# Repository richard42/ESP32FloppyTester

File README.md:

# ESP32_FloppyTester README

## What it is

The ESP32_FloppyTester is an open-source hardware/software project which aims to create a software-based floppy drive controller and tester with very low-cost hardware.  The materials cost for the interface board is under 10 dollars, and aside from a floppy drive cable the only other part necessary is an ESP32 development board, which can also be had for under 10 dollars.

The user communicates with the ESP32_FloppyTester via a serial monitor program on a PC or laptop, connected to the ESP32 development board by a USB cable.

The user gives commands to the ESP32_FloppyTester through the serial terminal, and as the desired operations are performed, statistics and results are sent back to the user.

The focus of this project is creating an easily-hackable tool which can be used in the diagnosis and repair of vintage 3.5" and 5.25" floppy drives.

## What it is NOT

The ESP32_FloppyTester is not designed to read or write disk image files for copying or preservation of digital media.  There are numerous projects already available which serve this function well.  Before creating the ESP32_FloppyTester, I purchased and used the KryoFlux, the FluxEngine, and the GreaseWeazle. These are all very capable products for recording and capturing data from floppy drives.

The focus of this project is to give the user very low-level control over the operation of a floppy drive so that if it is defective, the nature and root cause of the defect(s) may be determined and remedied.

## Contents

* [Hardware Warning](#hardware-warning)
* [Setup](#setup)
* [Basic Usage](#basic-usage)
* [Advanced Usage](#advanced-usage)
* [Caveats](caveats)

### Hardware Warning

There is one important flaw with the current interface board design, and users must be aware of this.

When the ESP32 microcontroller is being flashed by the ESP-IDF development system, all of its pins go into a high-impedance state with pull-up resistors.

As a result, all of the output lines will go active on any connected floppy drive. In particular, the SELECT, MOTOR ON, SIDE 1, and WRITE GATE lines will all be active during the ESP32 flashing process.

Because of this, if there is a disk inserted into the connected floppy drive, and it is not write protected, the track on side 1 which is under the drive head will be erased.

As a workaround, the user should always make sure that the drive has no disk in it when re-flashing the ESP32 software.

### Setup

To build the interface board, you may send the Gerber files in the "hardware" sub-directory to a printed-circuit board manufacturer such as PCBWay or JLCPCB. Order the remaining parts from digi-key and solder the board together once it all arrives. The "doc" sub-folder contains a Bill of Materials and pictures of the finished product.

The next step is to set up the [arduino IDE software](https://www.arduino.cc/en/software) and configure it for your ESP32 board. Then just load up the ESP32_FloppyTest.ino source code in your Arduino IDE and click the "Upload" button to compile the code and flash the ESP32 device. (But make sure there is no floppy disk in the drive, if you have one connected!)

Before connecting a drive the first time, it is good to check your soldering with the `TEST INPUT` and `TEST OUTPUT` commands.

When in the `TEST INPUT` mode, the software will poll for changes on any input pins and print the names and states of the pins when they change. You may use a jumper wire to bridge each input pin to a 5-volt supply, and observe the change via the serial monitor.

In the `TEST OUTPUT` mode, each output pin will oscillate with a binary pattern corresponding to the number of the pin. This pattern may be observed by connecting an oscilloscope to each output pin in turn. This test mode should never be used when a floppy drive is connected to the 34-pin connector, or **bad** things may happen.

Either test mode may be exited by sending a blank line or any characters to the ESP32.

### Basic Usage

Use the `HELP` command to view a list of all supported commands.

The floppy drive hardware interface, though common across many different drives and vintage computer systems, uses 5 different pins for selecting a particular drive and turning on its motor. The software currently defaults to a *shugart*-style interface with drive 0, such as would be configured for an internal drive on an Amiga computer. PC/Atari drives use different pins for drive selection, and so the user must use the `DETECT PINS` command to set the correct pins before anything else will work.

The `DETECT PINS` command activates each pin individually, and requests feedback from the user based upon how it affects the status of the floppy drive. At each step, the user must tell the ESP32_FloppyTester if the drive light has been illuminated, or if the motor has been activated. After answering all 5 prompts, the software will configure itself to properly address your floppy drive, and all of the other commands should then work.  If the detection fails and the drive light or motor never comes on, this indicates a failure in the drive's selection or motor control circuitry.

The next diagnostic step is to use the `DETECT RPM` command. A floppy disk must be inserted for this to work.  This command will enable the motor and begin sampling the INDEX pin, printing out the current drive RPM speed once per second. If this command fails, it indicates a problem with the index hole detection circuitry, or no floppy disk in the drive.

The final basic drive test can be performed with the `SEEK TEST` command. This will cause the drive to seek outwards until the TRACK0 line goes active, and then seek back and forth several times and ensure that track 0 is reached each time after returning there. If this command fails, there is likely to be a problem with the stepper motor drive circuitry or the track 0 detection mechanism.

### Advanced Usage

After all of the basic drive tests have passed, the user can move on to more advanced testing. The full command list is as follows:

```    HELP           - display this help message.
    TEST INPUT     - activate input test mode, and print level changes on input lines.
    TEST OUTPUT    - activate output test mode, and drive output pins with binary pin numbers.
    DETECT PINS    - toggle select lines to determine drive wiring/jumper setup.
    DETECT RPM     - spin up motor and calculate spindle speed from index pulses.
    DETECT STATUS  - show status of Track0, Write Protect, and Disk Change signal.
    MOTOR ON/OFF   - activate or de-activate motor 1
    SEEK HOME      - move to track 0.
    SEEK TEST      - test head seeking and track 0 detection.
    SEEK <X>       - seek head to track X.
    SEEK           - display current track number.
    SIDE <X>       - use side X (0 or 1) for single-sided commands.
    SIDE           - display current side number.
    GEOMETRY ...   - set/show current disk format and geometry. Examples:
             IBM   <SS/DS> <X> <Y> - set IBM format, single/double sided, X tracks, Y sectors.
             ATARI <SS/DS> <X> <Y> - set Atari format, single/double sided, X tracks, Y sectors.
             AMIGA                 - set Amiga format, 2 sides, 80 tracks, 11 sectors.
             COMMODORE             - set Commodore format, 1 side, 35 tracks, 17-21 sectors.
    TRACK READ     - read current track and print decoded data summary (requires formatted disk).
    TRACK ERASE    - erase current track and validate erasure (destroys data on disk).
    TRACK WRITE ...- write track data with current format and given pattern (destroys data on disk).
                ZEROS     - all sector data is binary 0 (MFM 4us intervals).
                ONES      - all sector data is binary 1 (MFM 4us intervals).
                SIXES     - all sector data is alternating bits (MFM 6us intervals).
                EIGHTS    - all sector data is alternating bits (MFM 8us intervals).
                RANDOM    - all sector data is random.
    TRACK RWTEST   - write and verify current track with 4 different patterns (destroys data on disk).\r\n");
    DISK READ      - read all tracks on disk and display track/sector status.
    DISK ERASE     - erase all tracks on the disk (destroys data on disk).
    DISK WRITE ... - write all tracks on disk with current format and given pattern (destroys data on disk).
    DISK RWTEST    - write and verify all tracks on disk with 4 different patterns (destroys data on disk).
```
#### DETECT STATUS
The `DETECT STATUS` command may be used to read the state of 3 input lines, which can indicate if the write protect switch/LED and the disk change circuitry (if supported by the drive) is working.

#### MOTOR ON
The user may activate the motor using the `MOTOR ON` command, and then the other commands will leave the motor running after they complete. This could be useful if a particular drive takes longer than the specified 0.5 seconds to settle after motor startup.

#### TRACK READ
The `TRACK READ` command captures the disk pulses from one revolution at the current head position, generates some statistics about the pulse timing intervals, and tries to decode any sector data found. This command is affected by the current drive geometry. The drive geometry must be set to "amiga" if reading amiga disks, or the default IBM if reading IBM or Atari ST disks. The output from the `TRACK READ` command looks like this:

```Track read complete; recorded 37967 flux transitions.
90% pulse interval spread is 0.7 microseconds.
Pulse Distance  Count   Average   Variance
     000004 us  18596   3.981 us  0.00324 us
     000005 us      1   4.988 us  0.00000 us
     000006 us  14598   6.025 us  0.00341 us
     000007 us      1   7.012 us  0.00000 us
     000008 us   4769   8.012 us  0.00459 us
     000030 us      1   29.712 us  0.00000 us
Double Density MFM track detected.
Found Index Access Marker (track start).
IBM Sector ID: Cylinder 0, Side 0, Sector 1, CRC=ca6f (GOOD)
IBM Sector data: 512 bytes with CRC=3cde (GOOD)
IBM Sector ID: Cylinder 0, Side 0, Sector 2, CRC=9f3c (GOOD)
IBM Sector data: 512 bytes with CRC=0f18 (GOOD)
IBM Sector ID: Cylinder 0, Side 0, Sector 3, CRC=ac0d (GOOD)
IBM Sector data: 512 bytes with CRC=b1b1 (GOOD)
IBM Sector ID: Cylinder 0, Side 0, Sector 4, CRC=359a (GOOD)
IBM Sector data: 512 bytes with CRC=0751 (GOOD)
IBM Sector ID: Cylinder 0, Side 0, Sector 5, CRC=06ab (GOOD)
IBM Sector data: 512 bytes with CRC=e9f6 (GOOD)
IBM Sector ID: Cylinder 0, Side 0, Sector 6, CRC=53f8 (GOOD)
IBM Sector data: 512 bytes with CRC=bb59 (GOOD)
IBM Sector ID: Cylinder 0, Side 0, Sector 7, CRC=60c9 (GOOD)
IBM Sector data: 512 bytes with CRC=320e (GOOD)
IBM Sector ID: Cylinder 0, Side 0, Sector 8, CRC=70f7 (GOOD)
IBM Sector data: 512 bytes with CRC=6da6 (GOOD)
IBM Sector ID: Cylinder 0, Side 0, Sector 9, CRC=43c6 (GOOD)
IBM Sector data: 512 bytes with CRC=ff82 (GOOD)
9 IBM sectors read.
```

The first line tells the total number of pulses received (flux transitions detected) during the track read. Normally, with a 720k disk this will be in the range of 15,000 to 40,000.  The data is encoded on the floppy disk by varying the time between adjacent pulses. For an MFM-encoded double-density disks, nearly all of the pulses should be either 4, 6, or 8 microseconds apart.

The "pulse interval spread" is a statistical metric which tells us how much variation exists between the pulse timings. For a formatted disk with data written along the entire track, this value will be in the 0.5-1.5 microsecond range. For a track which has been completely erased, this value will be much higher, in the 9-10 microsecond range.

Next, a histogram tells us how many pulse intervals fell into each 1-microsecond range. Again with an MFM-formatted double-density disk, we expect to see the vast majority of the pulse intervals at 4, 6, and 8 microseconds and very few in the other time ranges.

After the histogram, any decoded sector data will be printed. If you expect to see track information here, but there's nothing, and the histogram looks good, make sure that you have set the correct encoding format (IBM/Amiga) with the `GEOMETRY` command.

#### DISK READ
Using the `DISK READ` command, you can get an overview of all the sectors on the disk.  The output looks like this:

```Command> DISK READ
Found track 0 after stepping 0.0 tracks.
Reading disk sides 0 and 1.
 0 (37964 0.7) MFM  9 Sectors: OOO OOO OOO OOO OOO OOO OOO OOO OOO  |  (37911 0.7) MFM  8 Sectors: --- OOO OOO OOO OOO OOO OOO OOO OOO 
 1 (38001 0.7) MFM  8 Sectors: --- OOO OOO OOO OOO OOO OOO OOO OOO  |  (37859 0.7) MFM  8 Sectors: --- OOO OOO OOO OOO OOO OOO OOO OOO 
 2 (37856 0.7) MFM  8 Sectors: --- OOO OOO OOO OOO OOO OOO OOO OOO  |  (37846 0.7) MFM  8 Sectors: --- OOO OOO OOO OOO OOO OOO OOO OOO 
 3 (37896 0.7) MFM  8 Sectors: --- OOO OOO OOO OOO OOO OOO OOO OOO  |  (38010 0.7) MFM  8 Sectors: --- OOO OOO OOO OOO OOO OOO OOO OOO 
 4 (37953 0.7) MFM  8 Sectors: --- OOO OOO OOO OOO OOO OOO OOO OOO  |  (37851 0.7) MFM  8 Sectors: --- OOO OOO OOO OOO OOO OOO OOO OOO 
 5 (37913 0.7) MFM  8 Sectors: --- OOO OOO OOO OOO OOO OOO OOO OOO  |  (37917 0.7) MFM  8 Sectors: --- OOO OOO OOO OOO OOO OOO OOO OOO 
 6 (37851 0.7) MFM  8 Sectors: --- OOO OOO OOO OOO OOO OOO OOO OOO  |  (37865 0.7) MFM  8 Sectors: --- OOO OOO OOO OOO OOO OOO OOO OOO 
 7 (37896 0.7) MFM  8 Sectors: --- OOO OOO OOO OOO OOO OOO OOO OOO  |  (37998 0.7) MFM  8 Sectors: --- OOO OOO OOO OOO OOO OOO OOO OOO 
 8 (37863 0.7) MFM  8 Sectors: --- OOO OOO OOO OOO OOO OOO OOO OOO  |  (37900 0.7) MFM  8 Sectors: --- OOO OOO OOO OOO OOO OOO OOO OOO 
 9 (37843 0.7) MFM  8 Sectors: --- OOO OOO OOO OOO OOO OOO OOO OOO  |  (37952 0.7) MFM  8 Sectors: --- OOO OOO OOO OOO OOO OOO OOO OOO 
10 (37921 0.7) MFM  8 Sectors: --- OOO OOO OOO OOO OOO OOO OOO OOO  |  (37926 0.7) MFM  8 Sectors: --- OOO OOO OOO OOO OOO OOO OOO OOO 
11 (37910 0.7) MFM  8 Sectors: --- OOO OOO OOO OOO OOO OOO OOO OOO  |  (37894 0.7) MFM  8 Sectors: --- OOO OOO OOO OOO OOO OOO OOO OOO 
12 (37892 0.7) MFM  8 Sectors: --- OOO OOO OOO OOO OOO OOO OOO OOO  |  (37912 0.7) MFM  8 Sectors: --- OOO OOO OOO OOO OOO OOO OOO OOO 
13 (37958 0.7) MFM  8 Sectors: --- OOO OOO OOO OOO OOO OOO OOO OOO  |  (37955 0.7) MFM  8 Sectors: --- OOO OOO OOO OOO OOO OOO OOO OOO 
14 (37951 0.7) MFM  8 Sectors: --- OOO OOO OOO OOO OOO OOO OOO OOO  |  (37939 0.7) MFM  8 Sectors: --- OOO OOO OOO OOO OOO OOO OOO OOO 
15 (37899 0.7) MFM  8 Sectors: --- OOO OOO OOO OOO OOO OOO OOO OOO  |  (37882 0.7) MFM  8 Sectors: --- OOO OOO OOO OOO OOO OOO OOO OOO 
16 (37934 0.7) MFM  8 Sectors: --- OOO OOO OOO OOO OOO OOO OOO OOO  |  (37857 0.7) MFM  8 Sectors: --- OOO OOO OOO OOO OOO OOO OOO OOO 
17 (18787 10.7) MFM  0 Sectors: --- --- --- --- --- --- --- --- ---  |  (37892 2.8) MFM  0 Sectors: --- --- --- --- --- --- --- --- --- 
18 (34117 3.7) MFM  0 Sectors: --- --- --- --- --- --- --- --- ---  |  (36187 2.9) MFM  0 Sectors: --- --- --- --- --- --- --- --- --- 
```

The left half of this shows side 0, while the right half shows side 1.  At the start of each track, in parentheses, are the values for the number of flux transitions in the track, and the 90% pulse interval spread statistic.

Following this is the encoding type (MFM), the number of sectors read in the track, and 3 letters indicating the status of each sector in the track.  Three dashes or hyphens means that the sector was not detected. Otherwise, each letter is either an `O` (meaning good) or an `X` (meaning bad).

The first letter indicates whether or not the positional metadata (track number and side number) in the sector header matches with the sector's position on the disk. The second letter indicates whether the CRC or checksum value in the sector header matches with the header's actual CRC.  And the third letter indicates whether the sector's data CRC or checksum match with the checksum calculated from the data read from disk.

#### DISK RWTEST

The `DISK RWTEST` command is useful for stress testing the floppy drive and a disk to determine if it is susceptible to any particular patterns in the pulse timings.

With this command, each track is written and then read back four times, with a different data pattern each time. The first pattern uses all 4 microsecond pulse timings for the sector data. The second pattern uses all 6 microsecond pulses, and the third uses all 8 microsecond pulses.  The last data pattern starts with random sector data bytes and writes out the pulses corresponding to these random byte values.

The output of this command will look like this:

```Found track 0 after stepping 79.0 tracks.
Testing disk sides 0 and 1.
 0: OOOO OOOO OOOO OOOO OOOO OOOO OOOO OOOO OOOO | OOOO OOOO OOOO OOOO OOOO OOOO OOOO OOOO OOOO
 1: OOOO OOOO OOOO OOOO OOOO OOOO OOOO OOOO OOOO | OOOO OOOO OOOO OOOO OOOO OOOO OOOO OOOO OOOO
...
```

The leftmost number here is the track number. Then we have 4 letters for each sector, one letter for each data pattern.  If the letter is an `O`, then the data was successfully read back for that sector with that data pattern. If it is an `X`, then the sector data CRC didn't match, indicating likely data corruption. If it is an `x`, then the sector data was good but the sector header's CRC or metadata values didn't match.

### Caveats

There are many.

* This software and hardware comes with no warranty of any kind.
* Read the [Hardware Warning](#hardware-warning) again.
* Only Double Density disks are currently supported. The ESP32 is fast enough to handle HD disks as well, but it is likely that a significant amount of code refactoring would be necessary to support HD drives due to the limited amout of RAM in the ESP32.

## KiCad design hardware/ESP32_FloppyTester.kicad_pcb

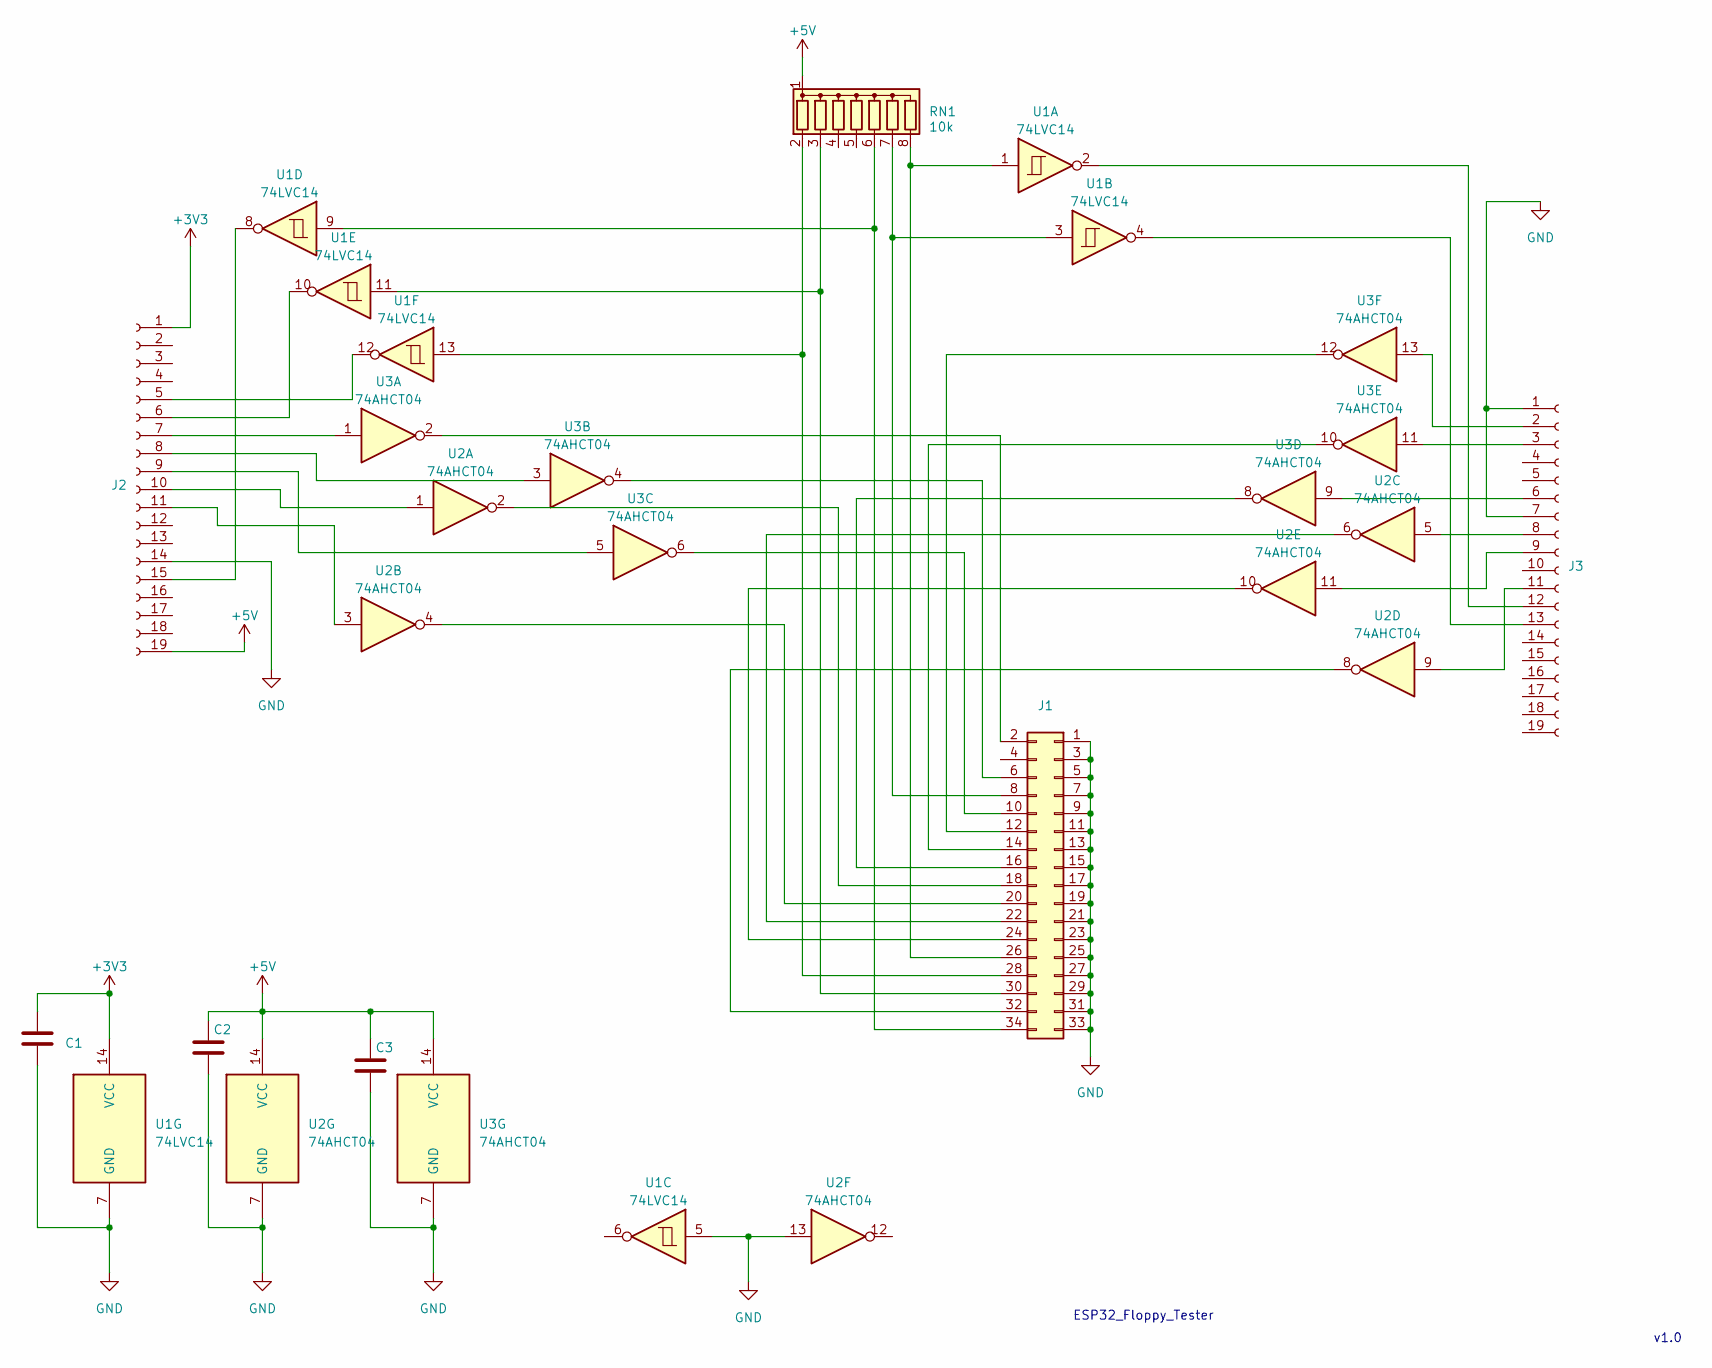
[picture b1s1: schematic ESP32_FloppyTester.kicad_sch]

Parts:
C1, C2, C3: 0.1uF; C_0805_2012Metric
J1: Conn_02x17_Odd_Even; PinHeader_2x17_P2.54mm_Vertical
J2, J3: Conn_01x19_Socket; PinSocket_1x19_P2.54mm_Vertical
RN1: 10k; R_Array_SIP8
U1: 74LVC14; SOIC-14_3.9x8.7mm_P1.27mm
U2, U3: 74AHCT04; SOIC-14_3.9x8.7mm_P1.27mm

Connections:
+3V3: C1.2, J2.1, U1.14 (VCC)
+5V: C2.1, C3.1, J2.19, RN1.1 (common), U2.14 (VCC), U3.14 (VCC)
GND: C1.1, C2.2, C3.2, J1.1, J1.3, J1.5, J1.7, J1.9, J1.11, J1.13, J1.15, J1.17, J1.19, J1.21, J1.23, J1.25, J1.27, J1.29, J1.31, J1.33, J2.14, J3.1, J3.7, U1.5, U1.7 (GND), U2.7 (GND), U2.13, U3.7 (GND)
unnamed: J1.2, U3.2
unnamed: J1.6, U3.4
unnamed: J1.8, RN1.7 (R6), U1.3
unnamed: J1.10, U3.6
unnamed: J1.12, U3.12
unnamed: J1.14, U3.10
unnamed: J1.16, U3.8
unnamed: J1.18, U2.2
unnamed: J1.20, U2.4
unnamed: J1.22, U2.6
unnamed: J1.24, U2.10
unnamed: J1.26, RN1.8 (R7), U1.1
unnamed: J1.28, RN1.2 (R1), U1.13
unnamed: J1.30, RN1.3 (R2), U1.11
unnamed: J1.32, U2.8
unnamed: J1.34, RN1.6 (R5), U1.9
unnamed: J2.5, U1.12
unnamed: J2.6, U1.10
unnamed: J2.7, U3.1
unnamed: J2.8, U3.3
unnamed: J2.9, U3.5
unnamed: J2.10, U2.1
unnamed: J2.11, U2.3
unnamed: J2.15, U1.8
unnamed: J3.2, U3.13
unnamed: J3.3, U3.11
unnamed: J3.6, U3.9
unnamed: J3.8, U2.5
unnamed: J3.9, U2.11
unnamed: J3.11, U2.9
unnamed: J3.12, U1.2
unnamed: J3.13, U1.4

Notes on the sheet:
ESP32_Floppy_Tester
v1.0

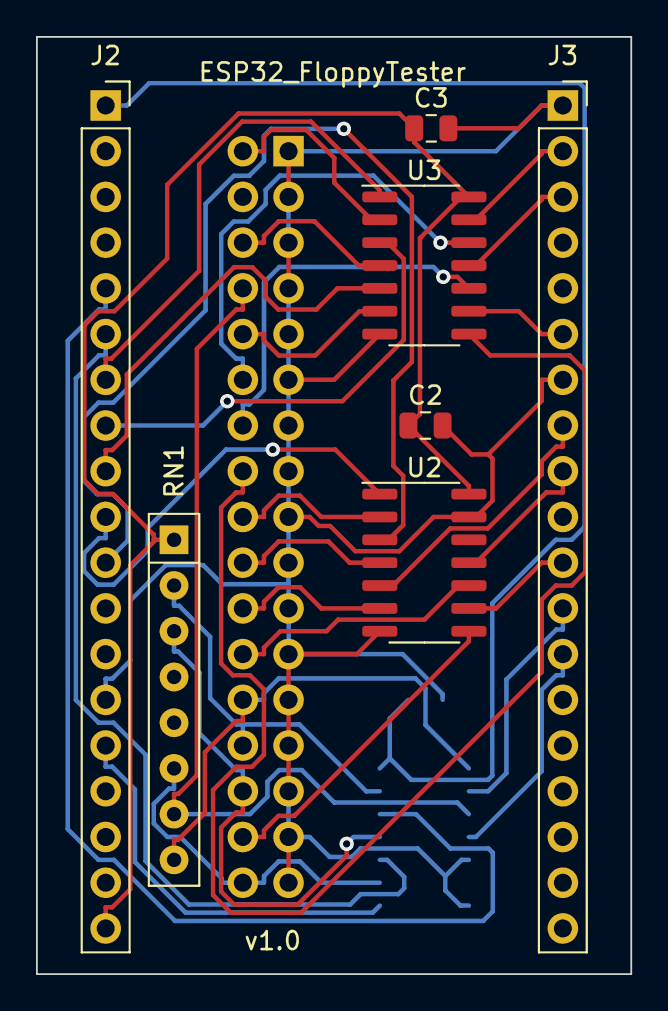
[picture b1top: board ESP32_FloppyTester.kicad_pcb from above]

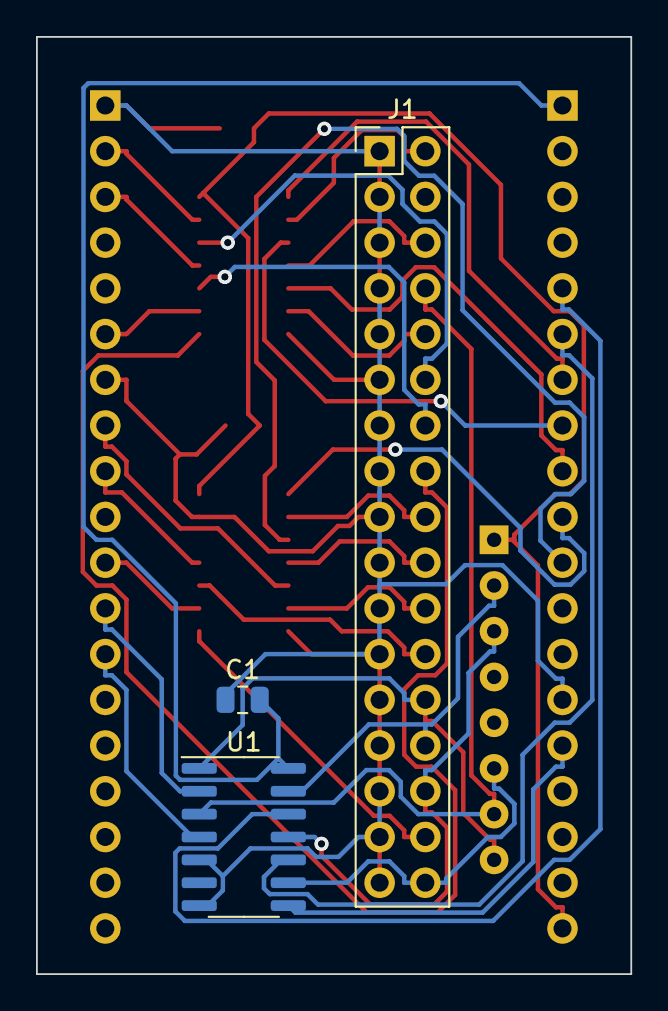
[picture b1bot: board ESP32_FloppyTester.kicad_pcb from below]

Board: 2 copper layers, 33.0 x 52.1 mm, 10 parts (3 on the bottom side), 35 nets.

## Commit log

2024-01-21 initial draft of basic floppy tester program skeleton with a few working features
2024-01-22 add copyright message. add delay before printing startup prompt. use MCPWM module for capture signal edge times. add interrupt handler to record data in sample buffer. implement "test rpm" command.
2024-01-22 disable interrupt watchdog timer so that we can get extremely precise timings for disk track writes in the future. Implement extremely precise inline assembly function for adding a time delay in unit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
2024-01-22 implement TEST SEEK and SEEK <X> commands
2024-01-23 achieve 192kb sample buffer by breaking into 12 16k buffers allocated on heap and using macro to access samples. add skeleton for "test read" command
2024-01-23 prevent seeking failures by disabling interrupts while outputting seek pulses
2024-01-28 bump sample buffer size up to 13 4k-sample pages. in TEST READ command, activate RDATA sampling and edge time recording during one pass between index pulses
2024-01-29 add some basic statistical analysis and track type detection in TEST READ
2024-01-29 refactor everything to use buffers of 16-bit edge time deltas instead of 32-bit time values, to save memory and because we are really only interested in the deltas anyway
2024-02-06 clear interrupt bit earlier in ISR to avoid spurious interrupt calls. Add new rough draft class for parsing/decoding MFM-encoded data on IBM floppy disks
2024-02-06 completely re-write MFM parsing logic, so that it actually works now
2024-02-06 disable FreeRTOS system timer tick interrupt while reading floppy data, or we will lose pulses
2024-02-07 add code for calculating and validating CRC values
2024-02-07 code refactoring: move gpio_init/reset to top of file, break all of the command logic into separate functions, remove reset and status commands.
2024-02-07 rename commands. add separate 'seek home' command
2024-02-07 rename variables and refactor logic so that if user turns on the drive motor, don't wait settling time at start of each command, and don't turn motor off at end
2024-02-08 add SIDE command
2024-02-08 implement DETECT STATUS command and first half of TRACK ERASE command
2024-02-09 implement second part of TRACK ERASE command. add function for calculating 90% interval spread, and display in TRACK READ also
2024-02-10 add basic functionality for parsing Amiga tracks
2024-02-10 add commands to tell current track and side
2024-02-10 add commands to set and show drive format geometry
2024-02-10 use format geometry when recording and parsing track data, to improve Amiga sector recognition by reading track with 10% overlap
2024-02-11 print number of tracks read. add some hacks to work around some really bad compiler bug observed in ReadSectorBytesAmiga()
2024-02-11 rename loop variable in hopes of getting around compiler bug (didnt work - it still must be declared volatile)
2024-02-11 fix problem which prevented Amiga MFM parser from reading first sector after the gap - it is preceded by many many zeros
2024-02-11 Add TRACK WRITE command. Implement logic for writing tracks to disk with index-aligned (IBM) geometry, using CPU cycle counter. Implement EncoderMFM class with initial support for 9-sector double den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
2024-02-11 renamed DecoderMFM to CodecMFM
2024-02-11 implement DISK READ command and helper functions for formatting metadata as text. Add code in CodecMFM to capture metadata while parsing track
2024-02-13 implement DISK ERASE command
2024-02-13 implement DISK WRITE command
2024-02-13 implement DISK RWTEST command
2024-02-13 move source code into subfolder
2024-02-13 arduino is kind of stupid and requires the parent directory of the .ino source file to have the same name as the file without the .ino
2024-02-13 add LICENSE file and put source code under GPLv3
2024-02-13 add kicad project files and output gerber files for interface board
2024-02-13 add pictures and documents
2024-02-13 move test_track_patterns() function
2024-02-13 add README file
2024-02-14 it is not actually necessary to decrement these track numbers outside of the loop, because there is an apparent compiler bug which keeps the loop variable at its last value before breaking the loop c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
2024-02-15 allow setting geometry for 81-83 tracks
2024-02-16 add support for writing 10/11 sector atari st disks (800k/880k) and 880k amiga disks
2024-02-16 split ATARI into its own format, and hard-code tracks to 80 and sectors to 9 for IBM
2024-02-16 add new command TRACK RWTEST
2024-02-16 bugfix: when generating amiga sector data, the sector number must be 0-based, not 1-based
2024-02-16 bugfix: account for bit swizzling while writing an EIGHTS pattern for an Amiga disk
2024-11-10 in DETECT PINS, add support for Coco drives which use the same pin for both Select and Motor-on.
2024-11-11 add support for reading and writing 360k Coco/IBM 5.25 disks
2024-11-15 Add new Geometry option named COMMODORE, using 1 side, 35 tracks, 21 sectors, and new FMT_C64 format. This format (like the Amiga) does not need to synchronize with the index hole. Increase maximum s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
2024-11-17 In DecoderGCR::DetectEncoding(), handle corner cases where bit patterns results in very small 2x or 3x wavelength peaks. In DecoderGCR::ReadSectorBytesC64(), allow later good sector read to overwrite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
2025-08-25 accept sector DAM values of F8-FB instead of just FB, as used on TRS-80 disks. Correctly calculate 256-byte sector data CRCs when writing MFM 18-sector formats
2025-08-25 update markdown readme file
